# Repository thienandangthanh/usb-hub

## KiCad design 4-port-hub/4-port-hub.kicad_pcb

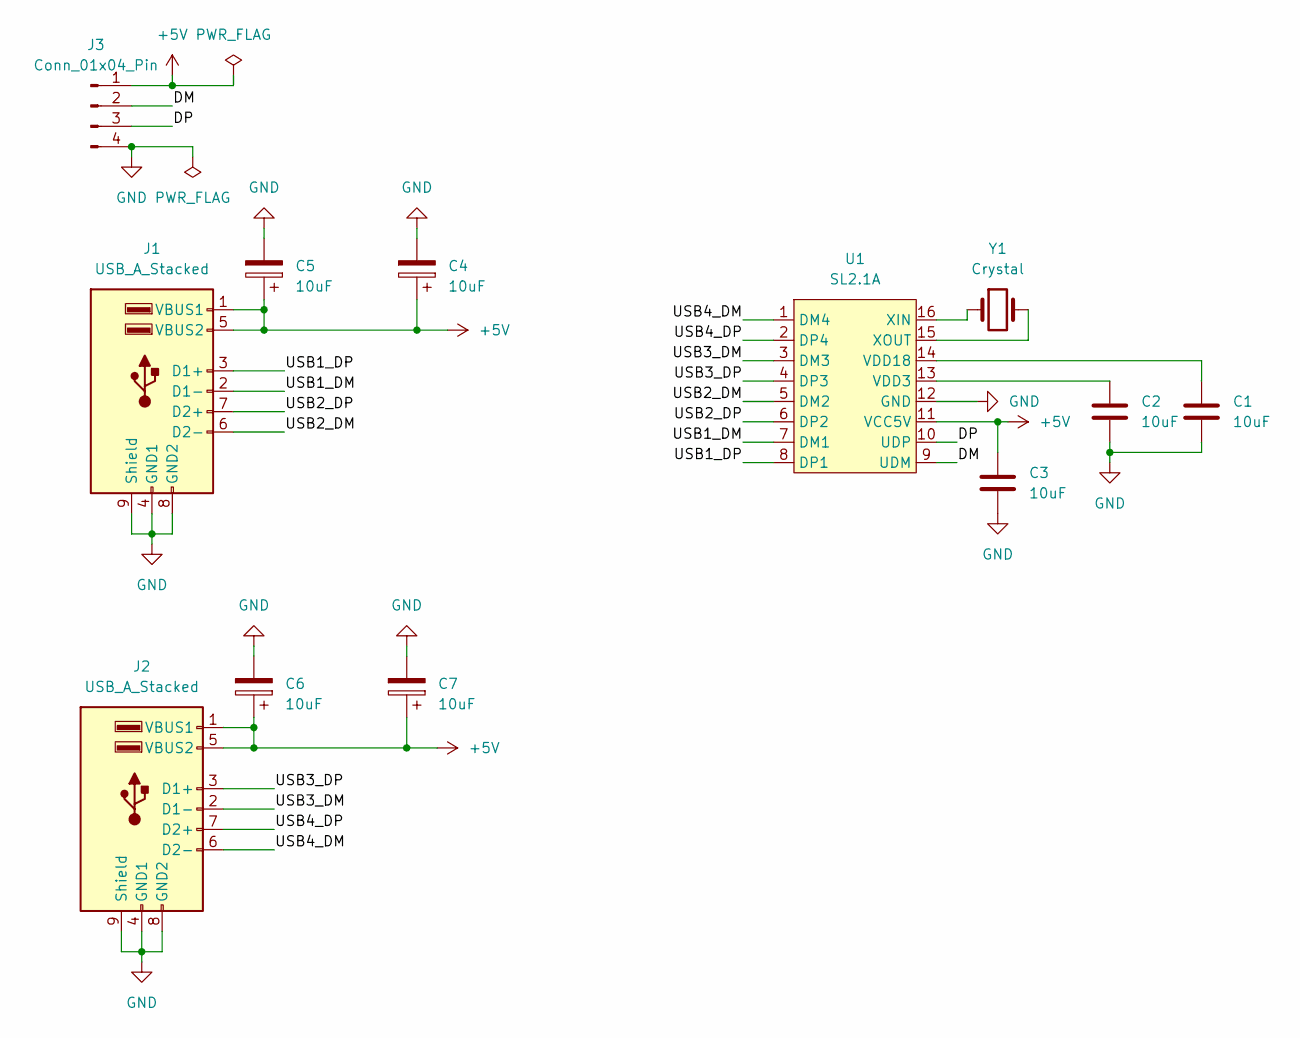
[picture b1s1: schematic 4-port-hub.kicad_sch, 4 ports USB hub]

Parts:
C1, C2, C3: 10uF; C_0805_2012Metric_Pad1.18x1.45mm_HandSolder
C4, C5, C6, C7: 10uF; C_1206_3216Metric_Pad1.33x1.80mm_HandSolder
J1, J2: USB_A_Stacked; USB3_A_Molex_48393-001
J3: Conn_01x04_Pin; Molex_KK-254_AE-6410-04A_1x04_P2.54mm_Vertical
U1: SL2.1A; SOP-16_3.9x9.9mm_P1.27mm
Y1: Crystal; Crystal_HC49-4H_Vertical

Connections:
+5V: C3.1, C4.1, C5.1, C6.1, C7.1, J1.1 (VBUS1), J1.5 (VBUS2), J2.1 (VBUS1), J2.5 (VBUS2), J3.1, U1.11 (VCC5V)
/DM: J3.2, U1.9 (UDM)
/DP: J3.3, U1.10 (UDP)
/USB1_DM: J1.2 (D1-), U1.7 (DM1)
/USB1_DP: J1.3 (D1+), U1.8 (DP1)
/USB2_DM: J1.6 (D2-), U1.5 (DM2)
/USB2_DP: J1.7 (D2+), U1.6 (DP2)
/USB3_DM: J2.2 (D1-), U1.3 (DM3)
/USB3_DP: J2.3 (D1+), U1.4 (DP3)
/USB4_DM: J2.6 (D2-), U1.1 (DM4)
/USB4_DP: J2.7 (D2+), U1.2 (DP4)
GND: C1.2, C2.2, C3.2, C4.2, C5.2, C6.2, C7.2, J1.4 (GND1), J1.8 (GND2), J1.9 (Shield), J2.4 (GND1), J2.8 (GND2), J2.9 (Shield), J3.4, U1.12 (GND)
unnamed: C2.1, U1.13 (VDD3)
unnamed: C1.1, U1.14 (VDD18)
unnamed: U1.16 (XIN), Y1.1
unnamed: U1.15 (XOUT), Y1.2

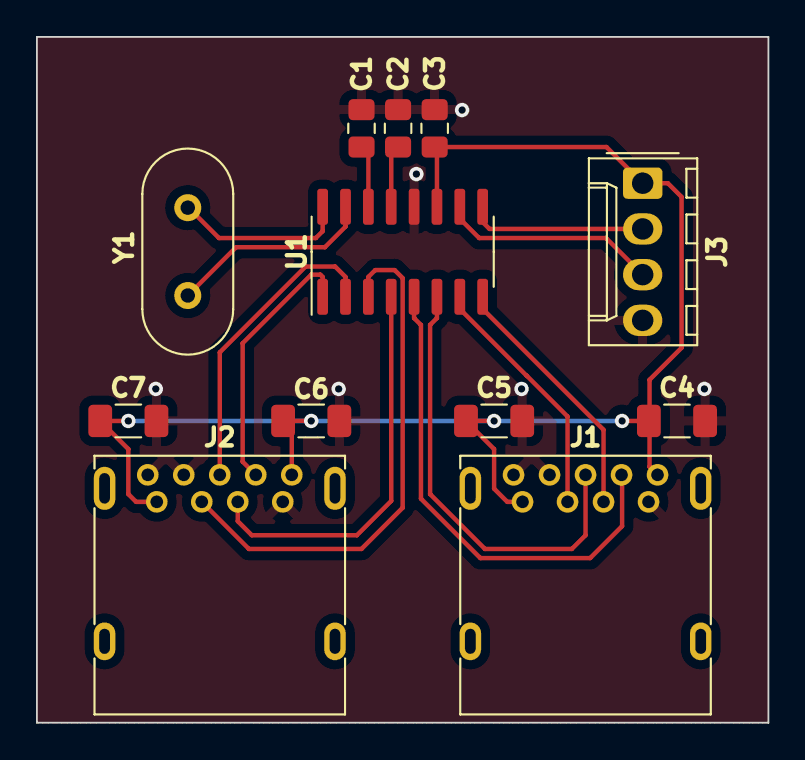
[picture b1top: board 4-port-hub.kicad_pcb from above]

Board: 2 copper layers, 40.6 x 38.1 mm, 12 parts (0 on the bottom side), 16 nets.

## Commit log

2023-08-09 Add KiCad .gitignore
2023-08-09 Add 4-port-hub design
2023-08-12 Improve signal routes
2023-08-12 Move 4-port-hub project to SL2.1A
    Reason: to make clear that design is used with SL2.1A IC
